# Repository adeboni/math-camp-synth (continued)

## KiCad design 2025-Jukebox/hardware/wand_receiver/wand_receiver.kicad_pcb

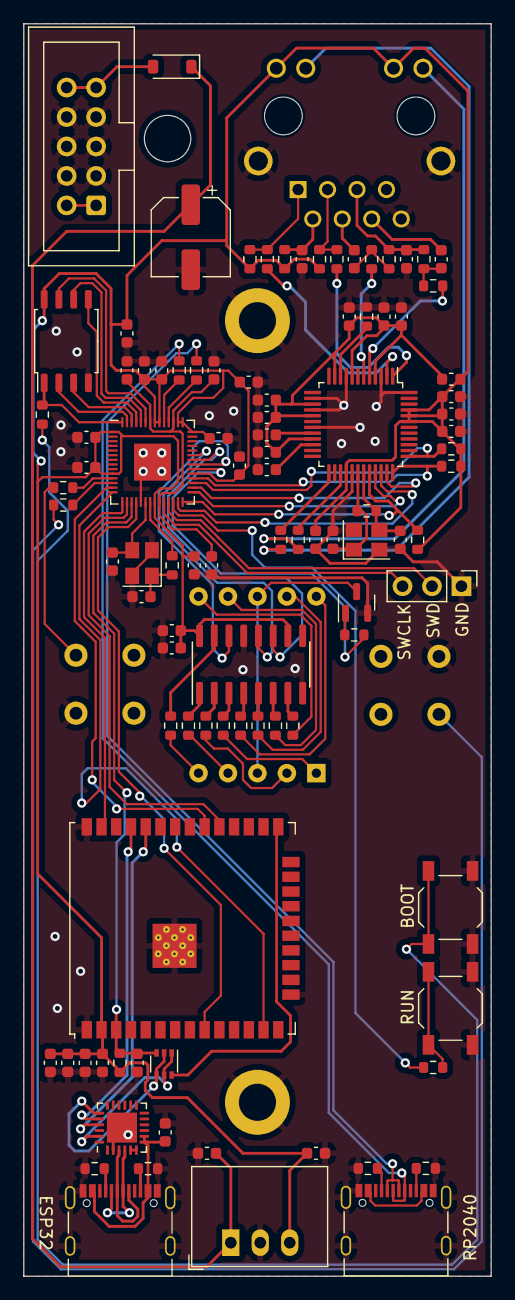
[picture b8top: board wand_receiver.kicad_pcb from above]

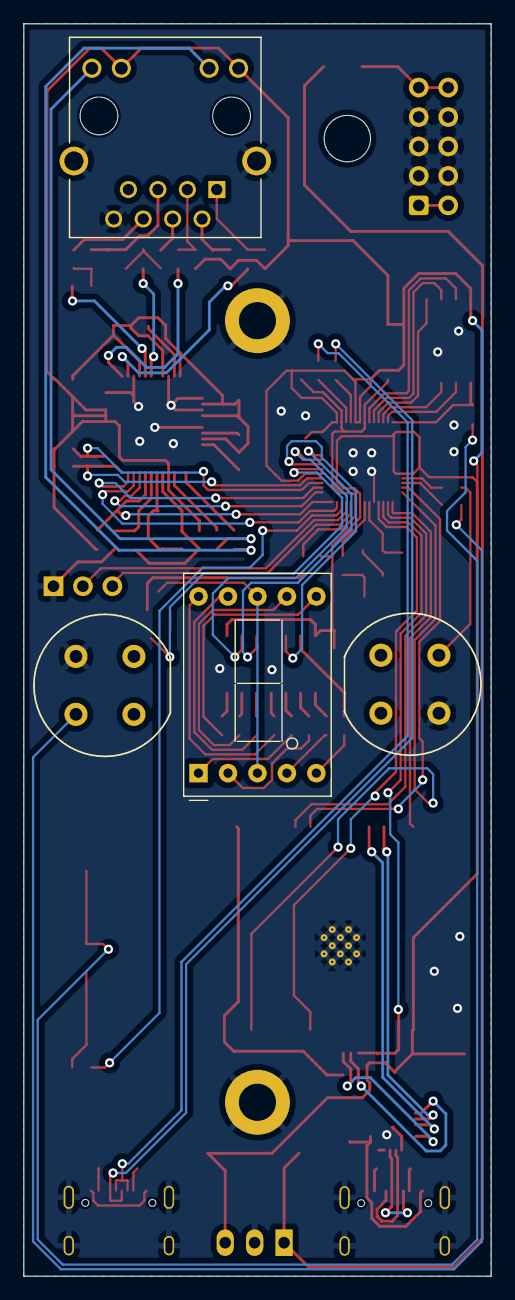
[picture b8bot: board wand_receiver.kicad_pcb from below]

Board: 2 copper layers, 40.3 x 108.0 mm, 105 parts (4 on the bottom side), 98 nets.

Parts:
C1, C2, C3, C20, C26, C27, C29: 10u; C_0603_1608Metric
C4, C5, C7, C8, C9, C10, C11, C12, C13, C14, C15, C16, C21, C28, C30, C31, C32, C33, C34, C35, C36, C37, C38, C71: 100n; C_0603_1608Metric
C6, C39, C40: 1u; C_0603_1608Metric
C17, C19: 22p; C_0603_1608Metric
C18, C22: 10n; C_0603_1608Metric
C23, C24: 6.8n; C_0603_1608Metric
C25: 100u; CP_Elec_6.3x5.4
C52, C56: 27p; C_0603_1608Metric
D1: SM4007; D_SOD-123
FB1: FerriteBead; L_0603_1608Metric
H1, H2: MountingHole_Pad; MountingHole_3.2mm_M3_DIN965_Pad
J1, J4: USB_C_Receptacle_USB2.0; USB_C_Receptacle_Palconn_UTC16-G
J2: Conn_02x05_Odd_Even; IDC-Header_2x05_P2.54mm_Vertical
J3: SI-46001-F; BEL_SI-46001-F
J5: Conn_01x03; PinHeader_1x03_P2.54mm_Vertical
Q1: MUN5214DW1T1G; SOT-363_SC-70-6
Q2: MMBT3904; SOT-23
R1, R4, R30, R32: 5.1k; R_0603_1608Metric
R2, R5, R31, R47, R52, R53: 1k; R_0603_1608Metric
R3, R6, R10, R12: 10k; R_0603_1608Metric
R7, R8, R9, R11: 4.7; R_0603_1608Metric
R13, R14, R15, R16: 49.9; R_0603_1608Metric
R17: 1M; R_0603_1608Metric
R18, R19: 470; R_0603_1608Metric
R20: 12.4k; R_0603_1608Metric
R21: 10; R_0603_1608Metric
R22, R23, R24, R25, R26, R27, R28, R29: 100; R_0603_1608Metric
R33, R34: 27; R_0603_1608Metric
SW1, SW2: SW_Push; Push_E-Switch_KS01Q01
SW3, SW4: SW_Push; SW_SPST_TL3342
U1: CP2104; QFN-24-1EP_4x4mm_P0.5mm_EP2.6x2.6mm
U2: W5500; LQFP-48_7x7mm_P0.5mm
U3: ESP32-WROOM-32U
U4: R-783.3-1.0; Converter_DCDC_RECOM_R-78E-0.5_THT
U6: 74HC595; SOIC-16_3.9x9.9mm_P1.27mm
U7: RP2040; QFN-56-1EP_7x7mm_P0.4mm_EP3.2x3.2mm
U8: SC52-11; D1X8K
U11: W25Q128JVS; SOIC-8_5.23x5.23mm_P1.27mm
Y1: 25MHz; Crystal_SMD_3225-4Pin_3.2x2.5mm
Y2: 12MHz; Crystal_SMD_3225-4Pin_3.2x2.5mm

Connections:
+1V1: C30.1, C31.1, C39.1, U7.23 (DVDD), U7.45 (VREG_VOUT), U7.50 (DVDD)
+3.3V: C1.1, C2.1, C3.1, C4.1, C7.1, C8.1, C9.1, C10.1, C27.1, C28.1, C29.1, C32.1, C33.1, C34.1, C35.1, C36.1, C37.1, C38.1, C40.1, C71.1, FB1.1, J3.10, J3.12, R3.1, R6.1, R10.1, R12.1, R13.2, R14.2, R21.2, U2.28 (VDD), U2.43 (PMODE2), U2.44 (PMODE1), U2.45 (PMODE0), U3.2 (VDD), U4.3 (OUT), U6.10 (~SRCLR), U6.16 (VCC), U7.1 (IOVDD), U7.10 (IOVDD), U7.22 (IOVDD), U7.33 (IOVDD), U7.42 (IOVDD), U7.43 (ADC_AVDD), U7.44 (VREG_IN), U7.48 (USB_VDD), U7.49 (IOVDD), U11.8 (VCC)
+3.3VA: C11.1, C12.1, C13.1, C14.1, C15.1, C16.1, FB1.2, U2.4 (AVDD), U2.8 (AVDD), U2.11 (AVDD), U2.15 (AVDD), U2.17 (AVDD), U2.21 (AVDD)
+12V: C25.1, C26.1, D1.1 (K), U4.1 (IN)
/CS_0: R6.2, U2.32 (~SCS), U7.28 (GPIO17)
/INTn: R10.2, U2.36 (~INT), U7.32 (GPIO21)
/MISO_0: U2.34 (MISO), U7.27 (GPIO16)
/MOSI_0: U2.35 (MOSI), U7.30 (GPIO19)
/QSPI_SCLK: U7.52 (QSPI_SCLK), U11.6 (CLK)
/QSPI_SD0: U7.53 (QSPI_SD0), U11.5 (DI(IO0))
/QSPI_SD1: U7.55 (QSPI_SD1), U11.2 (DO(IO1))
/QSPI_SD2: U7.54 (QSPI_SD2), U11.3 (IO2)
/QSPI_SD3: U7.51 (QSPI_SD3), U11.7 (IO3)
/QSPI_SS: R53.2, U7.56 (QSPI_SS), U11.1 (~CS)
/RSTn: R12.2, U2.37 (~RST), U7.31 (GPIO20)
/RUN: R52.1, U7.26 (RUN)
/SCK_0: U2.33 (SCLK), U7.29 (GPIO18)
/~USB_BOOT: R53.1, SW4.2
ACTn: R19.1, U2.27 (ACTLED)
BUTTON_1: R2.2, U7.11 (GPIO8)
BUTTON_2: R5.2, U7.12 (GPIO9)
D+: J4.A6 (D+), J4.B6 (D+), R33.1
D-: J4.A7 (D-), J4.B7 (D-), R34.1
DTR: Q1.1 (E2), Q1.5 (B1), U1.23 (~DTR)
ESP_BUSY: U3.9 (IO33), U7.18 (GPIO15)
ESP_CS: U3.29 (IO5), U7.16 (GPIO13)
ESP_GPIO_0: Q1.6 (C2), U3.25 (IO0)
ESP_MISO: U3.37 (IO23), U7.15 (GPIO12)
ESP_MOSI: U3.13 (IO14), U7.14 (GPIO11)
ESP_RESET: C6.1, Q1.3 (C1), R3.2, U3.3 (EN), U7.17 (GPIO14)
ESP_SCK: U3.30 (IO18), U7.13 (GPIO10)
GND: C1.2, C2.2, C3.2, C4.2, C5.2, C6.2, C7.2, C8.2, C9.2, C10.2, C11.2, C12.2, C13.2, C14.2, C15.2, C16.2, C17.1, C18.1, C19.2, C20.2, C21.2, C22.1, C25.2, C26.2, C27.2, C28.2, C29.2, C30.2, C31.2, C32.2, C33.2, C34.2, C35.2, C36.2, C37.2, C38.2, C39.2, C40.2, C52.2, C56.2, C71.2, H1.1, H2.1, J1.A1 (GND), J1.A12 (GND), J1.B1 (GND), J1.B12 (GND), J1.S1 (SHIELD), J2.3, J2.4, J2.5, J2.6, J2.7, J2.8, J3.8, J3.SH, J4.A1 (GND), J4.A12 (GND), J4.B1 (GND), J4.B12 (GND), J4.S1 (SHIELD), J5.1, Q2.2 (E), R1.1, R4.2, R20.1, R30.1, R32.1, SW1.2, SW2.2, SW3.1, SW4.1, U1.2 (GND), U1.25 (GND), U2.3 (AGND), U2.9 (AGND), U2.14 (AGND), U2.16 (AGND), U2.19 (AGND), U2.29 (GND), U2.48 (AGND), U3.1 (GND), U3.15 (GND), U3.38 (GND), U3.39 (GND), U4.2 (GND), U6.8 (GND), U6.13 (~OE), U7.19 (TESTEN), U7.57 (GND), U11.4 (GND), Y1.2, Y1.4, Y2.2, Y2.4
LINKn: R18.1, U2.25 (LINKLED)
NUM_A: R28.1, U8.7 (A)
NUM_B: R29.1, U8.6 (B)
NUM_C: R23.1, U8.4 (C)
NUM_D: R24.1, U8.2 (D)
NUM_DIG1: R31.2, U7.34 (GPIO22)
NUM_DP: R22.1, U8.5 (DP)
NUM_E: R25.1, U8.1 (E)
NUM_EN: U6.12 (RCLK), U7.37 (GPIO25)
NUM_F: R27.1, U8.9 (F)
NUM_G: R26.1, U8.10 (G)
NUM_SCK: U6.11 (SRCLK), U7.36 (GPIO24)
NUM_SER: U6.14 (SER), U7.35 (GPIO23)
unnamed: C56.1, R47.2, Y2.1
unnamed: D1.2 (A), J2.9, J2.10
unnamed: J1.A5 (CC1), R4.1
unnamed: J1.B5 (CC2), R1.2
unnamed: J2.1, J2.2
unnamed: J3.9, R19.2
unnamed: J3.11, R18.2
unnamed: C23.2, J3.4 (RD+)
unnamed: C24.1, J3.6 (RD-)
unnamed: C22.2, J3.2 (TCT), R21.1
unnamed: J4.A5 (CC1), R30.2
unnamed: J4.B5 (CC2), R32.2
unnamed: J4.A4 (VBUS), J4.A9 (VBUS), J4.B4 (VBUS), J4.B9 (VBUS)
unnamed: J5.2, U7.25 (SWD)
unnamed: J5.3, U7.24 (SWCLK)
unnamed: Q2.1 (B), R31.1
unnamed: Q2.3 (C), U8.3 (CC), U8.8 (CC)
unnamed: R2.1, SW1.1
unnamed: R5.1, SW2.1
unnamed: R52.2, SW3.2
unnamed: J1.A6 (D+), J1.B6 (D+), U1.3 (D+)
unnamed: J1.A7 (D-), J1.B7 (D-), U1.4 (D-)
unnamed: U1.5 (VIO), U1.6 (VDD)
unnamed: C21.1, U2.22 (1V2O)
unnamed: R20.2, U2.10 (EXRES1)
unnamed: R9.1, U2.5 (RXN)
unnamed: R11.2, U2.6 (RXP)
unnamed: C20.1, U2.20 (TOCAP)
unnamed: R7.1, U2.1 (TXN)
unnamed: R8.2, U2.2 (TXP)
unnamed: C17.2, R17.2, U2.30 (XI/CLKIN), Y1.1
unnamed: C19.1, R17.1, U2.31 (XO), Y1.3
unnamed: R22.2, U6.15 (QA)
unnamed: R23.2, U6.1 (QB)
unnamed: R24.2, U6.2 (QC)
unnamed: R25.2, U6.3 (QD)
unnamed: R26.2, U6.4 (QE)
unnamed: R27.2, U6.5 (QF)
unnamed: R28.2, U6.6 (QG)
unnamed: R29.2, U6.7 (QH)
unnamed: R34.2, U7.46 (USB_DM)
unnamed: R33.2, U7.47 (USB_DP)
unnamed: C52.1, U7.20 (XIN), Y2.3
unnamed: R47.1, U7.21 (XOUT)
RCT: C18.2, J3.5 (RCT), R15.2, R16.2
RTS: Q1.2 (B2), Q1.4 (E1), U1.19 (~RTS)
RXD: U1.21 (TXD), U3.34 (RXD0/IO3)
RXN: C24.2, R9.2, R15.1
RXP: C23.1, R11.1, R16.1
TXD: U1.20 (RXD), U3.35 (TXD0/IO1)
TXN: J3.3 (TD-), R7.2, R13.1
TXP: J3.1 (TD+), R8.1, R14.1
VBUS: C5.1, J1.A4 (VBUS), J1.A9 (VBUS), J1.B4 (VBUS), J1.B9 (VBUS), U1.7 (REGIN), U1.8 (VBUS)

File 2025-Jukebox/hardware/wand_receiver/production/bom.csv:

Designator,Footprint,Quantity,Value,LCSC Part #
"C1, C2, C20, C26, C27, C29, C3",0603,7,10u,C96446
"C10, C11, C12, C13, C14, C15, C16, C21, C28, C30, C31, C32, C33, C34, C35, C36, C37, C38, C4, C5, C7, C71, C8, C9",0603,24,100n,C14663
"C17, C19",0603,2,22p,C1653
"C18, C22",0603,2,10n,C57112
"C23, C24",0603,2,6.8n,C1631
C25,CP_Elec_6.3x5.4,1,100u,C180946
"C39, C40, C6",0603,3,1u,C15849
"C52, C56",0603,2,27p,C1653
D1,D_SOD-123,1,SM4007,C64898
FB1,0603,1,FerriteBead,C1002
"J1, J4",USB_C_Receptacle_Palconn_UTC16-G,2,USB_C_Receptacle_USB2.0,C709357
Q1,SOT-363_SC-70-6,1,MUN5214DW1T1G,C136173
Q2,SOT-23,1,MMBT3904,C20526
"R1, R30, R32, R4",0603,4,5.1k,C23186
"R10, R12, R3, R6",0603,4,10k,C25804
"R11, R7, R8, R9",0603,4,4.7,C23164
"R13, R14, R15, R16",0603,4,49.9,C23185
R17,0603,1,1M,C22935
"R18, R19",0603,2,470,C23179
"R2, R31, R47, R5, R52, R53",0603,6,1k,C21190
R20,0603,1,12.4k,C22865
R21,0603,1,10,C22859
"R22, R23, R24, R25, R26, R27, R28, R29",0603,8,100,C22775
"R33, R34",0603,2,27,C25190
"SW3, SW4",SW_SPST_TL3342,2,SW_Push,C318884
U1,QFN-24-1EP_4x4mm_P0.5mm_EP2.6x2.6mm,1,CP2104,C47742
U11,SOIC-8_5.23x5.23mm_P1.27mm,1,W25Q128JVS,C97521
U2,LQFP-48_7x7mm_P0.5mm,1,W5500,C32843
U3,ESP32-WROOM-32U,1,ESP32-WROOM-32U,C328062
U6,SOIC-16_3.9x9.9mm_P1.27mm,1,74HC595,C5947
U7,QFN-56-1EP_7x7mm_P0.4mm_EP3.2x3.2mm,1,RP2040,C2040
Y1,Crystal_SMD_3225-4Pin_3.2x2.5mm,1,25MHz,C9006
Y2,Crystal_SMD_3225-4Pin_3.2x2.5mm,1,12MHz,C9002

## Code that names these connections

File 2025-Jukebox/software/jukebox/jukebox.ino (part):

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
#define SDA_PIN       2
#define SCL_PIN       3
#define BTN_Q7_PIN    5
#define BTN_CP_PIN    6
#define BTN_PL_PIN    7
#define SD_CLK_PIN    10
#define SD_CMD_PIN    11
#define SD_DAT3_PIN   13
#define SD_DAT2_PIN   14
#define SD_DAT1_PIN   15
#define SD_DAT0_PIN   12
#define WIZ_MISO_PIN  16
#define WIZ_CS_PIN    17
#define WIZ_SCK_PIN   18
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bool displayUpdating = false;

uint16_t volumeRaw = 0;
float volume = 0;

File file;
AudioFileSourceSD *sdSource;
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  Wire1.setSCL(SCL_PIN);
  Wire1.begin();

  pinMode(BTN_PL_PIN, OUTPUT);
  pinMode(BTN_Q7_PIN, INPUT);
  pinMode(BTN_CP_PIN, OUTPUT);

  pinMode(WIZ_RST_PIN, OUTPUT);
  digitalWrite(WIZ_RST_PIN, LOW);
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  out->udpBuffer[0] = PACKET_ID_AUDIO_DATA;
  memset(out->udpBuffer + 1, 128, UDP_AUDIO_BUFF_SIZE - 1);

  SPI1.setRX(SD_DAT0_PIN);
  SPI1.setTX(SD_CMD_PIN);
  SPI1.setSCK(SD_CLK_PIN);
  SPI1.setCS(SD_DAT3_PIN);
  SD.begin(SD_DAT3_PIN, SPI_FULL_SPEED, SPI1);

  for (int i = 0; i < 260; i++)
    for (int j = 0; j < MAX_SONG_NAME_LEN; j++)
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void checkButtons() {
  static unsigned long lastButtonCheck = 0;
  if (millis() - lastButtonCheck > 50) {
    digitalWrite(BTN_PL_PIN, LOW);
    digitalWrite(BTN_PL_PIN, HIGH);

    for (int i = 0; i < 8; i++) {
      uint8_t buttonState = digitalRead(BTN_Q7_PIN);
      if (buttonState && !buttonStates[i])
        buttonAction(i);
      buttonStates[i] = buttonState;
      digitalWrite(BTN_CP_PIN, HIGH);
      digitalWrite(BTN_CP_PIN, LOW);
    }
    lastButtonCheck = millis();
  }
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
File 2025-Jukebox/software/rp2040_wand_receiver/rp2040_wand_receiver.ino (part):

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
#define BTN_2_PIN     8
#define BTN_1_PIN     9
#define ESP_SCK_PIN   10
#define ESP_MOSI_PIN  11
#define ESP_MISO_PIN  12
#define ESP_CS_PIN    13
#define ESP_RST_PIN   14
#define ESP_RDY_PIN   15
#define WIZ_MISO_PIN  16
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  digitalWrite(SEG_DIG1_PIN, LOW);
  updateSegDisplay();

  pinMode(ESP_CS_PIN, OUTPUT);
  digitalWrite(ESP_CS_PIN, HIGH);
  pinMode(ESP_RDY_PIN, INPUT);
  pinMode(ESP_RST_PIN, OUTPUT);
  digitalWrite(ESP_RST_PIN, LOW);
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  delay(750);
  pinMode(ESP_RST_PIN, INPUT);

  SPI1.setRX(ESP_MISO_PIN);
  SPI1.setTX(ESP_MOSI_PIN);
  SPI1.setSCK(ESP_SCK_PIN);
  SPI1.setCS(ESP_CS_PIN);
  SPI1.begin();
}

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void slaveSelect() {
  while (digitalRead(ESP_RDY_PIN) == HIGH);
  SPI1.beginTransaction(spiSettings);
  digitalWrite(ESP_CS_PIN, LOW);
  for (unsigned long start = millis(); (digitalRead(ESP_RDY_PIN) != HIGH) && (millis() - start) < 5;);
}

void slaveDeselect() {
  digitalWrite(ESP_CS_PIN, HIGH);
  SPI1.endTransaction();
}

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
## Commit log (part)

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2022-08-22 initial upload
2022-12-08 Re-organized and added 2023 synth files
2022-12-08 Re-organized source code
2022-12-22 Added display adapter
2022-12-29 Added led meter and motor mount
2023-01-10 Re-organized files
2023-01-13 Added LED meter support
2023-01-23 minor bug fixes
2023-01-26 Revamped synth code
2023-07-27 Updated jukebox code
2023-07-27 Added new hardware
2023-07-30 Moved defines to another file
2023-07-30 Fixed occassional crashing when switching songs
2023-08-07 Added mode 2
2023-08-14 Finished mode 2
2023-08-14 Added power-off functionality
2023-08-21 Double animation times
2023-11-15 Updated to latest versions
2023-11-15 Added initial firmware
2023-11-15 Added wand and power supply files
2023-11-15 Added wand production files
2023-11-15 Changed 3.3v regulator
2023-11-17 Minor fixes
2023-11-17 Added a version of the wand with a mic
2023-11-17 Added decoupling cap to power supply toggle board
2023-11-19 Added power selection jumper for LED
2023-11-20 Updated power supply toggle pcb
2023-11-20 Simplified the MAX7313 code
2023-11-21 Added HID functionality
2023-11-22 Fixed HID issues
2023-11-22 Got sACN working
2023-11-22 Added LCD display code
2023-11-27 Added level shifters to LCD display signals
2023-11-27 Added rounded corners to power supply toggle PCB
2023-11-30 Fixed some LCD display bugs
2023-12-01 Updated schematic
2023-12-18 Added pi power board
2023-12-21 Added single board wand design
2023-12-21 Added some extra silkscreen indicators
2023-12-22 Updated wand PCBs
2023-12-22 Added 3D models
2023-12-27 Updated wand PCB
2024-01-04 Fixed wiring issue
2024-01-04 Updated gerbers
2024-01-05 Added neopixel boost converter board
2024-01-06 Updated wand firmware
2024-01-08 Minor updates to wand
2024-01-08 Updated wand code
2024-01-09 Renamed files
2024-01-26 Updates to neopixel circuit and ui board firmware
2024-01-30 Updated wand simulators
2024-02-06 Update wand speed calculation
2024-02-06 Added bongo test
2024-03-11 Optimized sACN code
2024-05-03 Made gatt version of the wand
2024-05-06 Updated pullup resistor values
2024-08-05 Added jukebox 2025 updates
2024-08-06 Added 2025 gerbers
2024-08-07 Added 2025 wand PCB design
2024-08-07 Added footprint for light pipe
2024-08-09 Replaced IMU with BNO055
2024-08-09 Added production files
2024-08-19 Changed button location
2024-10-01 Wand bug fixes
2024-10-02 Switched to TCP
2024-10-02 Added python client code
2024-10-03 Wand TCP bug fixes
2024-10-03 Updated packet format
2024-10-04 Added audio packet transitions
2024-10-07 Added test version of wand code
2024-10-08 Minor improvements
2024-10-09 Added UDP version of wand code
2024-10-09 Bug fixes
2024-11-11 Added new UI board firmware
2024-11-26 Added new PCBs
2024-12-11 Added mini tester UI
2024-12-11 Added jukebox firmware
2024-12-11 Jukebox bug fixes
2024-12-19 Added song pause functionality
2024-12-19 Reverted song pause feature
2025-01-12 Added ui_module
2025-01-13 Added UI features
2025-01-13 Added wand receiver firmware
2025-01-14 Display update fix
2025-01-15 Added wand code
2025-01-16 SPI bug fixes
2025-01-17 More SPI work
2025-01-21 Added animation support
2025-01-21 Added morse code support
2025-01-22 Added sound effects
2025-01-23 Added basic laser functionality
2025-01-24 Added support for three lasers
2025-01-25 Optimizations
2025-01-27 Added spirograph animation
2025-01-27 Added wand functionality
2025-01-28 Added bubble animation
2025-01-29 Added pong mode
2025-01-29 Minor additions
2025-01-29 Audio buffer fixes
2025-01-29 Audio viz fixes
2025-01-30 Add pong sound effect support
2025-01-30 Added equation support
2025-01-31 Updated xy_t struct
2025-02-03 Animation updates
2025-02-03 Commented out unused graphics
2025-02-03 Added wand rotation color
2025-02-03 Optimized audio visualizer
2025-02-04 Added sd card setup scripts
2025-02-04 Wand drawing fixes
2025-02-04 Wand math updates
2025-02-04 Updated ESP32 I2S driver
2025-02-05 Updated audio visualization
2025-02-05 Audio visualizer bug fixes
2025-02-06 Minor refactoring
2025-02-06 Optimized wand calibration
2025-02-06 Code cleanup
2025-03-03 Added button cable adapter
2025-06-17 Added all animation mode
2025-06-22 Changed animation lengths
